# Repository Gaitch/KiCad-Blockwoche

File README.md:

# KiCad-Blockwoche

## Installation

Unter Debian/Ubuntu kann KiCad mit den folgenden Befehlen installiert werden:

```sh
sudo apt install -t bookworm-backports kicad kicad-symbols kicad-footprints kicad-packages3d
```

---

## Tag 1

### Erste Schritte & Einstellungen

- Beim ersten Start die **globale Bibliotheksauswahl** auf Standard belassen.

### Steuerung

#### **Schaltplan-Editor**

- `A` – Bauteil hinzufügen
- `R` – Bauteil rotieren
- `X` – Bauteil spiegeln
- `W` – Draht/Wire zeichnen
- `E` – Bauteil bearbeiten
- `V` – Wert eines Bauteils ändern
- `G` – Bauteil verschieben (ohne Drähte zu trennen)
- `M` – Bauteil verschieben (mit Drähten)
- `Del` – Bauteil oder Draht löschen
- `Ctrl + Z` – Rückgängig machen

#### **PCB-Designer**

- `X` – Leiterbahnen (Traces) zeichnen
- `M` – Bauteil verschieben
- `R` – Bauteil rotieren
- `Ctrl + M` – Bauteil mit Relativbewegung verschieben
- `Ctrl + Z` – Rückgängig machen
- `Ctrl + Y` – Wiederholen
- `Del` – Element löschen

### Workflow

1. **Schaltplan zeichnen**
2. **Elektrische Regelprüfung (ERC) durchführen**
3. **Bauteile im Layout-Editor platzieren**
4. **Leiterbahnen routen** (komponenten verbinden)

### Wichtige Learnings

- Nach der **Zuweisung von Footprints**:
    - **Bauteile kopieren & Werte ändern, ohne die Teilenummern anzupassen, führt zu Problemen** bei der Fertigung.
- **Alle Power-Labels benötigen eine Power-Flag** (`pwr_flag`), damit die elektrische Regelprüfung keine Fehler meldet.

---

## Tag 2

### Arbeiten mit Symbolen

- Symbole können über den **Symbol-Importer** importiert werden.
- Nach dem Import sollte die Zuweisung von Symbolen zu den jeweiligen Footprints überprüft werden.

mit dem druekcen von e mit unselektiertem curses lassen sich die values aendern. und informationen wie 
datenblaetter und bestell informationen hinterlegen

### Shortcuts
p place pin  
e edit properties  

### Zusätzliche Tipps

- **Bibliotheksverwaltung:**
  - Falls benötigte Symbole oder Footprints fehlen, können eigene Bibliotheken angelegt werden.
  - Externe **KiCad-Bibliotheken** können über `Preferences → Manage Symbol Libraries` hinzugefügt werden.

### Datenbank

#### Treiber herunterladen und Installieren

```sh
sudo apt-get install iodbc
```

[https://www.unixodbc.org/](https://www.unixodbc.org/)

```sh
./configure
make
make install
```

[http://www.ch-werner.de/sqliteodbc/](http://www.ch-werner.de/sqliteodbc/)  
[http://www.ch-werner.de/sqliteodbc/html/index.html](http://www.ch-werner.de/sqliteodbc/html/index.html)

```sh
./configure && make
make install
```

#### Treiber Registrieren

```sh
sudo odbcinst -i -s -f /etc/odbc.ini
sudo odbcinst -i -d -f /etc/odbcinst.ini
```

Datenbank in KiCad hinzufügen. Wenn die Treiber korrekt installiert wurden, sollte keine Fehlermeldung auftauchen und die Komponenten tauchen mit dem gegebenen Namen in der Part-Selektion auf.

Neue Komponenten müssen dann über ein Datenbank-Tool in die Datenbank geschrieben werden. Die Symbole werden in KiCad erstellt und dann in der Datenbank verknüpft.

**Tabellenstruktur Datenbank**

| Feldname         | Beschreibung                                                    |
|-----------------|----------------------------------------------------------------|
| PartID          | Eindeutige ID des Bauteils in der Datenbank                    |
| Symbol         | Referenz auf das Schaltplansymbol                               |
| Footprint       | Zugehöriges Footprint-Modell für die Platine                   |
| Value           | Bauteilwert (z. B. Widerstandswert, Kapazität)                 |
| Designator      | Bezeichnung des Bauteils im Schaltplan (z. B. R1, C3, U5)      |
| Category        | Bauteilkategorie (z. B. Widerstand, Kondensator, IC)           |
| MFR             | Hersteller (Manufacturer) des Bauteils                         |
| MPN             | Herstellernummer (Manufacturer Part Number)                    |
| Rating          | Elektrische Spezifikationen des Bauteils (z. B. Spannung, Strom) |
| Remark         | Zusätzliche Anmerkungen oder Hinweise                          |
| Datasheet       | Link oder Pfad zum Datenblatt des Bauteils                     |
| Dist1           | Distributor 1 (Händler für das Bauteil)                        |
| Dist1PN         | Teilenummer bei Distributor 1                                  |
| Dist2           | Distributor 2                                                 |
| Dist2PN         | Teilenummer bei Distributor 2                                 |
| Dist3           | Distributor 3                                                 |
| Dist3PN         | Teilenummer bei Distributor 3                                 |
| Active          | Gibt an, ob das Bauteil aktiv oder abgekündigt ist             |
| Description     | Detaillierte Beschreibung des Bauteils                         |
| FootprintFilters | Filter für alternative Footprints                             |
| Keywords        | Stichworte für die Suche nach dem Bauteil                      |
| NoBom           | Gibt an, ob das Bauteil in die Stückliste (BOM) aufgenommen wird |
| SchematicOnly   | Bauteil existiert nur im Schaltplan, nicht auf der Platine     |
| Version         | Versionsnummer des Bauteils in der Datenbank                   |
| Created        | Datum der Erstellung des Bauteileintrags                        |
| Modified       | Datum der letzten Änderung des Bauteileintrags                  |

---

## Tag 3

### Arbeiten mit großen Schaltplänen

#### Schaltpläne über mehrere Seiten aufteilen
- Ermöglicht eine bessere **Strukturierung** und **Übersichtlichkeit**.
- Besonders hilfreich für **komplexe Schaltungen** mit vielen Komponenten.

#### Verwendung von Labels für Verbindungen
- Durch die Nutzung **gleichnamiger Labels** können Signale und Netze zwischen verschiedenen Seiten eines Schaltplans verbunden werden.
- Dies **ersetzt lange Drahtverbindungen** und sorgt für eine **saubere Darstellung**.  
  **Globale und lokale Labels beachten.**

#### Hierarchische Schaltpläne verwenden
- **Module** können in **separaten Hierarchieblöcken** organisiert werden.
- Erleichtert das **Wiederverwenden** von Schaltungsblöcken.
- **Verbessert die Lesbarkeit** des Schaltplans.

#### Netzklassen definieren
- **Netzklassen** helfen, verschiedene Signalarten (z. B. **Stromversorgung, Signalleitungen, Hochfrequenzleitungen**) zu organisieren.
- Dies erleichtert das **Einhalten von Design-Richtlinien** und **DRC-Prüfungen**. Diese können dann beim Layout eingestellt werden.

**(Zuweisungen ergänzen)**

#### BUS erstellen
- **Dicke blaue Leitung** zeichnen.
- **Label hinzufügen** und Bus-Elemente angeben (Example: `B0 - 13, CLK, IO`). Label name B[0..15]
- **Rechtsklick auf Bus → Unfold** wählen und dann die einzelnen Pins verbinden.
- **Bus-Aliase** können in den **Blatteigenschaften** neben dem Speichersymbol hinzugefügt werden.

#### Electrical Rule Check (ERC) Einstellungen
- **Input zu Input gibt keinen Fehler**. Diese sind einstellbar.

#### Capacity Bias Effect
- **Kapazitive Effekte durch Layout beachten.**
erklaeren was es macht.. hoehere spannung kleine kapazitaet

#### Pin Helper
- **Rechtsklick auf einen Pin → Pin Helper** wählen.
- **Label und Pin** direkt zuweisen.

### Footprints

- **3D-Modelle hinzufügen**, um Footprints visuell zu überprüfen.
- **Abmessungen aus Datenblättern entnehmen**.
- **Pads erstellen** mit dem Kreis-Icon.
- **Doppelklick auf ein Pad**, um **Größe und Position** festzulegen.
- **Eingabefelder unterstützen Berechnungen** (z. B. `5mm + 2mm`).

#### Zusätzliche Ebenen
- **Fab-Layer** für Fertigungsinformationen.
- **Silkscreen-Layer** für Beschriftungen auf der Platine.
- **Margin-Layer** zur Definition von Platinenrändern.

## Tag 4

### Vias
Bei Vias müssen einige Dinge beachtet werden, unter anderem:
- **Lagenaufbau und Möglichkeiten** → Vorab den **Produzenten** wählen und abklären.
- **Auswirkungen** → Kosten & Produktionszeit berücksichtigen.
- **Minimale Lochdurchmesser** → Typisch **0.3 mm**.
- **Restring** → Typisch **0.15 mm**.
- **Keine Vias im Pad** → Lötzinn fließt weg, außer verschlossen (→ teuer!).

---

### Einstellungen
**Pfad:** *File → Board-Setup*

#### **Physical Stackup**
- Anzahl **Layer** und deren **Eigenschaften/Konfiguration** festlegen.

#### **Constraints**
- Design-Regeln und **Mindestabstände** definieren.

#### **Netzklassen**
- **Gruppierung von Signalen** (z. B. **Power, GND, Signal**).

#### **Custom Rules**
- **Eigene Design-Regeln** für spezifische Anforderungen erstellen.

---

### PCB Designer

#### **Bauteile importieren**
- Fehlermeldungen beachten → zeigen **fehlende Footprints** oder andere **Komplikationen**.

#### **Schritt 1: Board zeichnen**
- **Edge Cuts** Layer für die **Platinenkontur** nutzen.

#### **Schritt 2: Bauteile platzieren**
- **Grob platzieren**, dann **Feinjustierung**.
- **Zentrale Komponenten zentrieren** (z. B. Mikrocontroller).
- **Ausrichtung beachten** → USB-Pins zum **USB-Stecker**.
- **Abstände einhalten**:
  - **Digitale und analoge Bereiche trennen**.
  - **Kurze Verbindungen für empfindliche Signale**.
  - **Kondensatoren möglichst nah an ICs platzieren**.

---

### **Tipps**
- **Nur Footprints selektierbar machen**, um **versehentliches Verschieben** von Verbindungen zu vermeiden.

Einige Bauteile wie Spannungsregulatoren oder Oszillatoren geben gewisse Anordnungen der Bauteile vor. Diese gemaess Datenblatt anordnen und verbinden.

---

### **Frage**
> Ist es möglich, nachträglich einen **Footprint** hinzuzufügen, sodass er automatisch mit bereits im **Schaltplan vorhandenen Bauteilen** synchronisiert wird?

## Tag 5

### **Flächen & Polygone (Filled Zones)**
- **Bereich zeichnen**, um eine gefüllte Kupferfläche zu erstellen.
- **Verbindung wählen** → Typischerweise **Speisung (VCC) oder Ground (GND)**.
- **Mit `B` neu generieren**, um die Zone zu aktualisieren.

#### **Eigenschaften der Zone anpassen**
1. **Zone anklicken** und **Eigenschaften öffnen**.
2. Unter **Pad Connection** den **Thermal Relief** Modus wählen.

---

### **Differentielles Layout für USB**
#### **Schritt 1: Netzlabels im Schematic Setup verwalten**
- **USB-Signale** in der **Netclass-Verwaltung** zuweisen.

#### **Schritt 2: Differenzpaar im Layout erstellen**
1. **`6` auf das Pad klicken**.
2. Zwei **parallele Leitungen** sollten automatisch erstellt werden.

---

## **Bill of Material (BOM)**
Die **Stückliste (Bill of Material, BOM)** enthält alle benötigten Bauteile für die Fertigung der Platine. Sie stellt sicher, dass alle Bauteile korrekt bestellt und bestückt werden.

### **Typische Informationen in der BOM**
- **Bauteilbezeichnung** (Designator, z. B. R1, C3, U5)
- **Bauteilwert** (z. B. 10kΩ, 100nF)
- **Footprint** (z. B. SMD0603, THT)
- **Hersteller & Bestellnummer** (MFR, MPN)
- **Distributor & Bestellnummer** (z. B. Mouser, Digikey, LCSC)
- **Anzahl der Bauteile** für die Fertigung

### **Export der BOM in KiCad**
Die BOM kann über **File → Fabrication Outputs → BOM** exportiert werden.  
Es gibt verschiedene **BOM-Plugins**, die z. B. eine CSV oder Excel-Datei generieren.

---

## **Gerber-Dateien**
**Gerber-Dateien** sind das standardisierte Format für die Herstellung von Leiterplatten. Sie enthalten die **grafische Darstellung** der verschiedenen PCB-Layer, die von Herstellern genutzt werden.

### **Typische Gerber-Dateien**
- **Leiterbahnen & Kupferflächen** (z. B. `Top_Copper`, `Bottom_Copper`)
- **Lötstopplack & Bestückungsdruck** (Solder Mask & Silkscreen)
- **Platinenumrisse** (Edge Cuts)

### **Gerber-Export in KiCad**
1. **File → Fabrication Outputs → Gerber**
2. **Alle relevanten Layer auswählen** (Top, Bottom, Silkscreen, Soldermask, etc.).
3. **Gerber-Dateien exportieren und in einem Viewer kontrollieren**.

---

## **Bohrdaten (Drill Files)**
Die **Bohrdaten** definieren alle Löcher, die auf der Platine gebohrt werden müssen. Sie sind besonders wichtig für bedrahtete Bauteile, Vias und Montagelöcher.

### **Typische Inhalte der Bohrdaten**
- **THT-Bohrungen** für bedrahtete Bauteile.
- **Vias** für Lagenverbindungen zwischen PCB-Schichten.
- **Montagelöcher** für Gehäuse oder Befestigungen.

### **Bohrdaten-Export in KiCad**
1. **File → Fabrication Outputs → Drill Files**
2. **Bohrdurchmesser & -typen überprüfen**.
3. **Bohrdateien zusammen mit den Gerber-Dateien an den Hersteller senden**.

---

## **Pick & Place Daten**
Die **Pick & Place Datei** enthält die **Positionen der Bauteile** für die automatische Bestückung mit Maschinen. SMT-Bauteile werden anhand dieser Datei automatisch auf die Platine gesetzt.

### **Typische Inhalte der Pick & Place Datei**
- **X- & Y-Koordinaten** der Bauteile.
- **Drehwinkel der Bauteile**.
- **Footprint & Referenzdesignator** (z. B. `R1`, `C3`).

### **Pick & Place-Export in KiCad**
1. **File → Fabrication Outputs → Footprint Position File**
2. **Format auswählen (CSV, TXT, etc.)**.
3. **Datei an den Bestücker senden**.

---

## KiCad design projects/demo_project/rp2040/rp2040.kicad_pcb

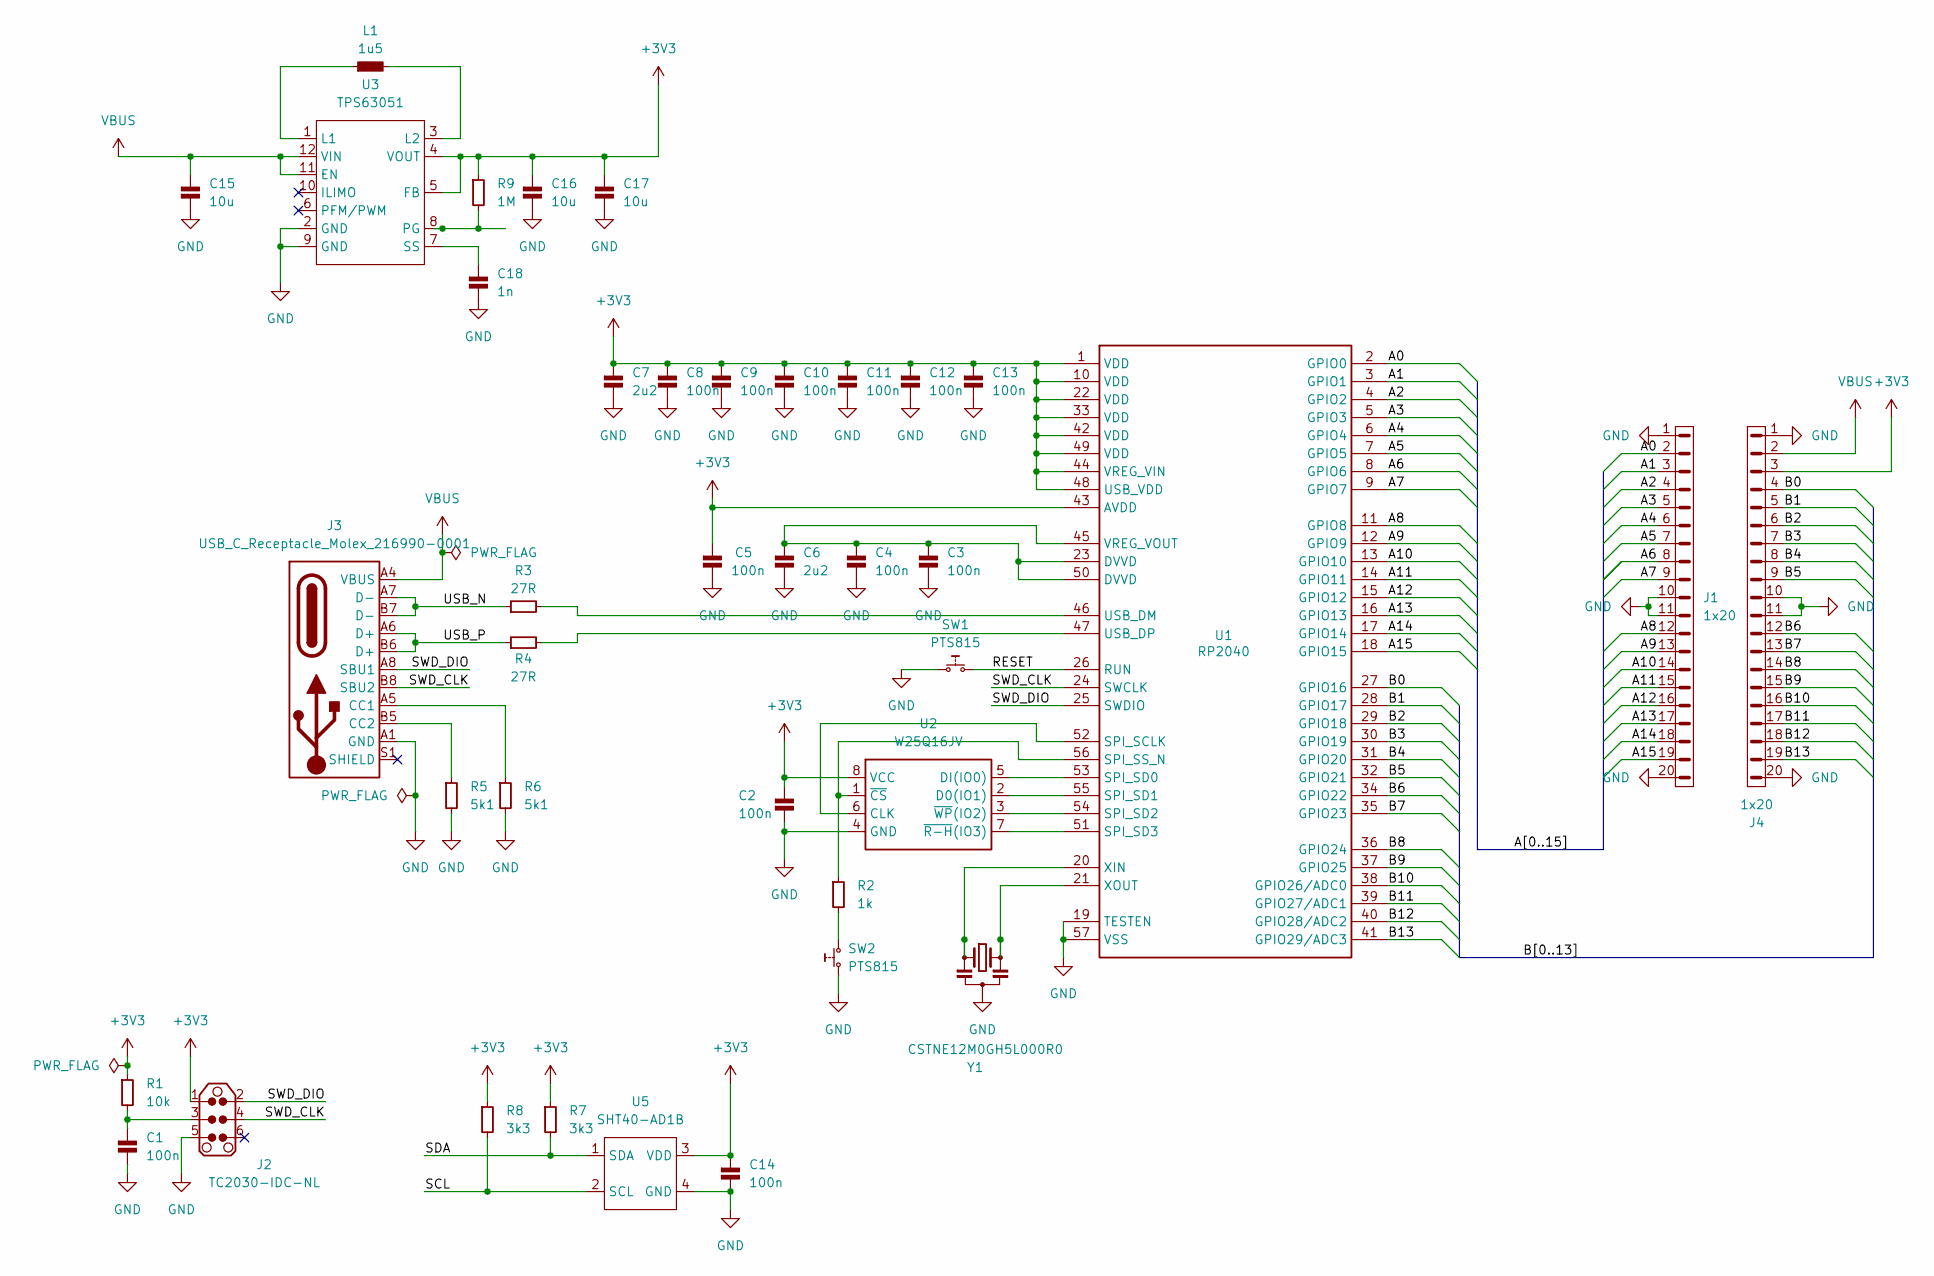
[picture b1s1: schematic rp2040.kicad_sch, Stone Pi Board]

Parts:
C1, C2, C3, C4, C5, C8, C9, C10, C11, C12, C13, C14: 100n; C_0402; Rating 16V, 10%, X7R; MFR# CL21B105KO5NNWC
C6, C7: 2u2; C_0402; Rating 10V, 20%, X5R; MFR# CC0402MRX5R6BB225
C15, C16, C17: 10u; C_0805; Rating 16V, 10%, X5R; MFR# CL21A106KOQNNNF
C18: 1n; C_0402; Rating 16V, 10%, X7R; MFR# CL05B102KO5NNWC
J1, J4: 1x20; PinHeader_1x20_P2.54mm_Vertical; Rating 3A; MFR# 61302011121
J2: TC2030-IDC-NL; MFR# TC2030-IDC-NL
J3: USB_C_Receptacle_Molex_216990-0001; USB_C_Receptacle_MidMnt_Molex_16_Contact_216990-0001; Rating 16 contacts, 1.25A; MFR# 216990-0001
L1: 1u5; L_3.2x2.5; Rating 4A, 20%, 61mOhm; MFR# SRP3212A-1R2M
R1: 10k; R_0402; Rating 50V, 62.5mW, 1%; MFR# RC0402FR-0710KL
R2: 1k; R_0402; Rating 50V, 62.5mW, 1%; MFR# RC0402FR-071KL
R3, R4: 27R; R_0402; Rating 50V, 62.5mW, 1%; MFR# RC0402FR-0727RL
R5, R6: 5k1; R_0402; Rating 50V, 62.5mW, 1%; MFR# RC0402FR-075K1L
R7, R8: 3k3; R_0402; Rating 50V, 62.5mW, 1%; MFR# RC0402FR-073K3L
R9: 1M; R_0402; Rating 50V, 62.5mW, 1%; MFR# RC0402FR-071ML
SW1, SW2: PTS815; TS02-66-Series; Rating -40˚C to 90˚C; MFR# PTS815SJM250SMTR
U1: RP2040; QFN-56-1EP_7x7mm_P0.4mm_EP3.2x3.2mm
U2: W25Q16JV; USON_2x3x0.6mm
U3: TPS63051; VQFN-12-1EP_2.5x2.5mm_P0.5mm; Rating –0.3 to 7; MFR# TPS63051YFFR
U5: SHT40-AD1B; Sensirion_DFN-4_1.5x1.5mm_P0.8mm_SHT4x_NoCentralPad; MFR# SHT40-AD1B-R2
Y1: CSTNE12M0GH5L000R0; Resonator_SMD_Murata_CSTxExxV-3Pin_3.0x1.1mm; Rating 12MHz, 0.07%; MFR# CSTNE12M0GH5L000R0

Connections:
+3V3: C2.1, C5.1, C7.1, C8.1, C9.1, C10.1, C11.1, C12.1, C13.1, C14.1, C16.1, C17.1, J2.1, J4.3, R1.1, R7.1, R8.1, R9.1, U1.1 (VDD), U1.10 (VDD), U1.22 (VDD), U1.33 (VDD), U1.42 (VDD), U1.43 (AVDD), U1.44 (VREG_VIN), U1.48 (USB_VDD), U1.49 (VDD), U2.8 (VCC), U3.4 (VOUT), U3.5 (FB), U5.3 (VDD)
/A0: J1.2, U1.2 (GPIO0)
/A1: J1.3, U1.3 (GPIO1)
/A2: J1.4, U1.4 (GPIO2)
/A3: J1.5, U1.5 (GPIO3)
/A4: J1.6, U1.6 (GPIO4)
/A5: J1.7, U1.7 (GPIO5)
/A6: J1.8, U1.8 (GPIO6)
/A7: J1.9, U1.9 (GPIO7)
/A8: J1.12, U1.11 (GPIO8)
/A9: J1.13, U1.12 (GPIO9)
/A10: J1.14, U1.13 (GPIO10)
/A11: J1.15, U1.14 (GPIO11)
/A12: J1.16, U1.15 (GPIO12)
/A13: J1.17, U1.16 (GPIO13)
/A14: J1.18, U1.17 (GPIO14)
/A15: J1.19, U1.18 (GPIO15)
/B0: J4.4, U1.27 (GPIO16)
/B1: J4.5, U1.28 (GPIO17)
/B2: J4.6, U1.29 (GPIO18)
/B3: J4.7, U1.30 (GPIO19)
/B4: J4.8, U1.31 (GPIO20)
/B5: J4.9, U1.32 (GPIO21)
/B6: J4.12, U1.34 (GPIO22)
/B7: J4.13, U1.35 (GPIO23)
/B8: J4.14, U1.36 (GPIO24)
/B9: J4.15, U1.37 (GPIO25)
/B10: J4.16, U1.38 (GPIO26/ADC0)
/B11: J4.17, U1.39 (GPIO27/ADC1)
/B12: J4.18, U1.40 (GPIO28/ADC2)
/B13: J4.19, U1.41 (GPIO29/ADC3)
/RESET: SW1.2, U1.26 (RUN)
/SCL: R8.2, U5.2 (SCL)
/SDA: R7.2, U5.1 (SDA)
/SWD_CLK: J2.4, J3.B8 (SBU2), U1.24 (SWCLK)
/SWD_DIO: J2.2, J3.A8 (SBU1), U1.25 (SWDIO)
/USB_N: J3.A7 (D-), J3.B7 (D-), R3.1
/USB_P: J3.A6 (D+), J3.B6 (D+), R4.1
GND: C1.2, C2.2, C3.2, C4.2, C5.2, C6.2, C7.2, C8.2, C9.2, C10.2, C11.2, C12.2, C13.2, C14.2, C15.2, C16.2, C17.2, C18.2, J1.1, J1.10, J1.11, J1.20, J2.5, J3.A1 (GND), J3.A12 (GND), J3.B1 (GND), J3.B12 (GND), J4.1, J4.10, J4.11, J4.20, R5.2, R6.2, SW1.1, SW2.1, U1.19 (TESTEN), U1.57 (VSS), U2.4 (GND), U3.2 (GND), U3.9 (GND), U5.4 (GND), Y1.2
unnamed: C1.1, J2.3, R1.2
unnamed: J3.A5 (CC1), R6.1
unnamed: J3.B5 (CC2), R5.1
unnamed: R2.2, SW2.2
unnamed: U1.52 (SPI_SCLK), U2.6 (CLK)
unnamed: U1.53 (SPI_SD0), U2.5 (DI(IO0))
unnamed: U1.55 (SPI_SD1), U2.2 (D0(IO1))
unnamed: U1.54 (SPI_SD2), U2.3 (~WP(IO2))
unnamed: U1.51 (SPI_SD3), U2.7 (~R-H(IO3))
unnamed: R2.1, U1.56 (SPI_SS_N), U2.1 (~CS)
unnamed: R3.2, U1.46 (USB_DM)
unnamed: R4.2, U1.47 (USB_DP)
unnamed: C3.1, C4.1, C6.1, U1.23 (DVVD), U1.45 (VREG_VOUT), U1.50 (DVVD)
unnamed: U1.20 (XIN), Y1.1
unnamed: U1.21 (XOUT), Y1.3
unnamed: L1.1, U3.1 (L1)
unnamed: L1.2, U3.3 (L2)
unnamed: R9.2, U3.8 (PG)
unnamed: C18.1, U3.7 (SS)
VBUS: C15.1, J3.A4 (VBUS), J3.A9 (VBUS), J3.B4 (VBUS), J3.B9 (VBUS), J4.2, U3.11 (EN), U3.12 (VIN)

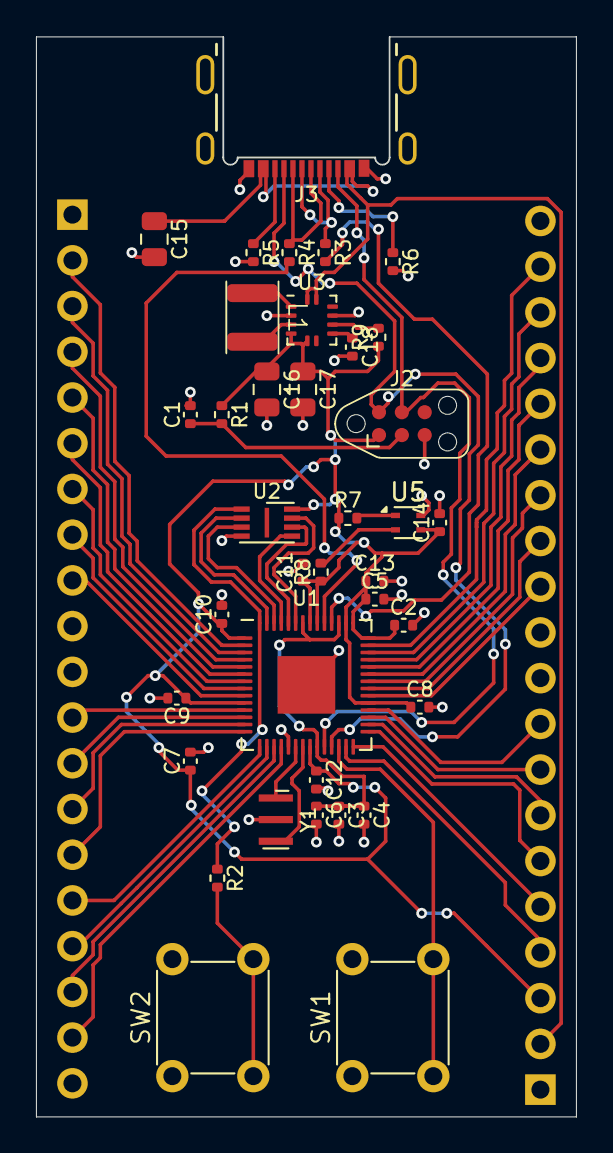
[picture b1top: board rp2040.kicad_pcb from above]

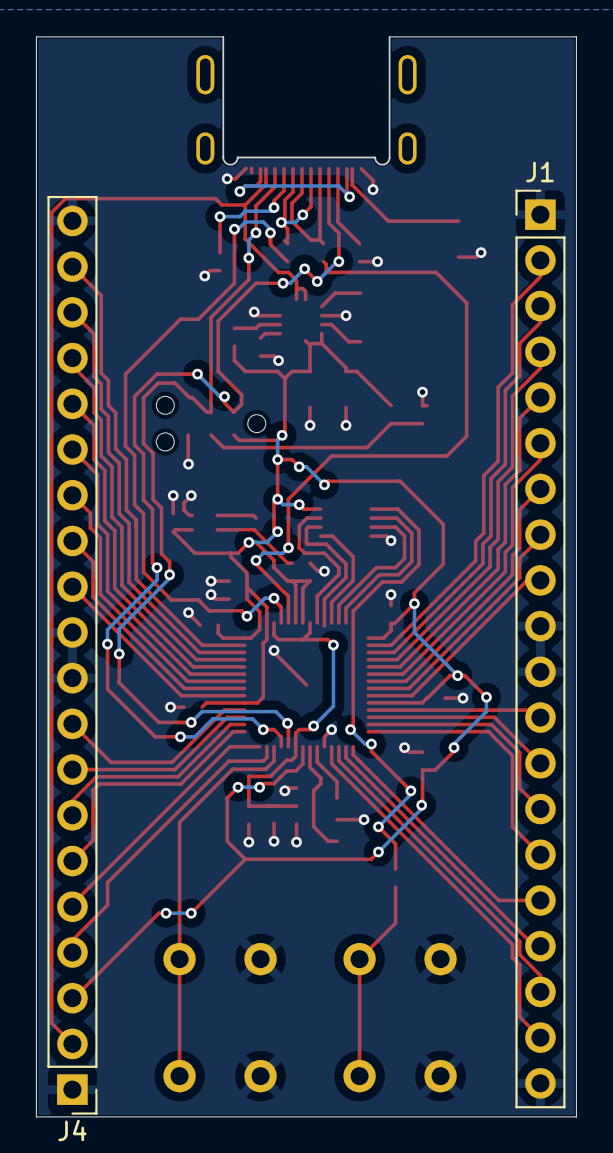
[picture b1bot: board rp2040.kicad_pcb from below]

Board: 2 copper layers, 30.0 x 60.0 mm, 39 parts (2 on the bottom side), 59 nets.

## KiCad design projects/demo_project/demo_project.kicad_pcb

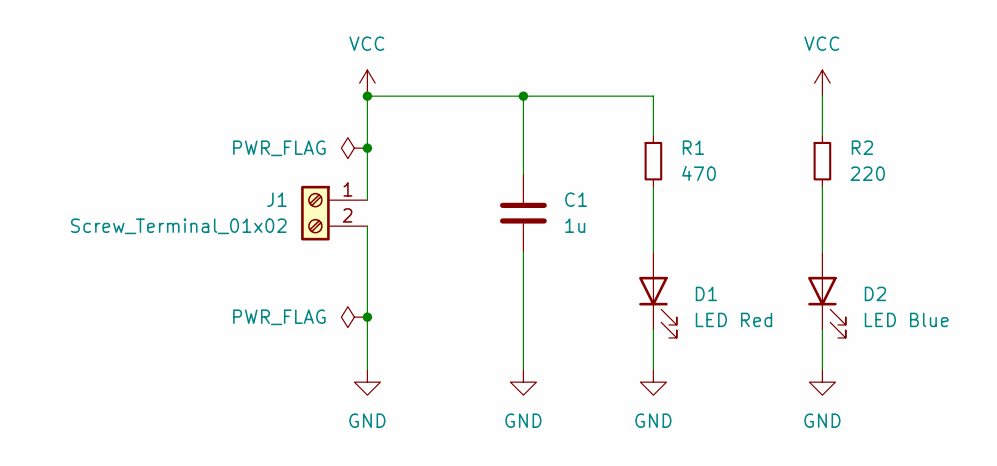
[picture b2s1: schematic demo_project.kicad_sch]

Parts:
C1: 1u; C_0805_2012Metric_Pad1.18x1.45mm_HandSolder
D1: LED Red; LED_0805_2012Metric_Pad1.15x1.40mm_HandSolder
D2: LED Blue; LED_0805_2012Metric_Pad1.15x1.40mm_HandSolder
J1: Screw_Terminal_01x02; TerminalBlock_Altech_AK300-2_P5.00mm
R1: 470; R_0805_2012Metric_Pad1.20x1.40mm_HandSolder
R2: 220; R_Axial_DIN0922_L20.0mm_D9.0mm_P25.40mm_Horizontal

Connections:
GND: C1.2, D1.1 (K), D2.1 (K), J1.2
unnamed: D1.2 (A), R1.2
unnamed: D2.2 (A), R2.2
VCC: C1.1, J1.1, R1.1, R2.1

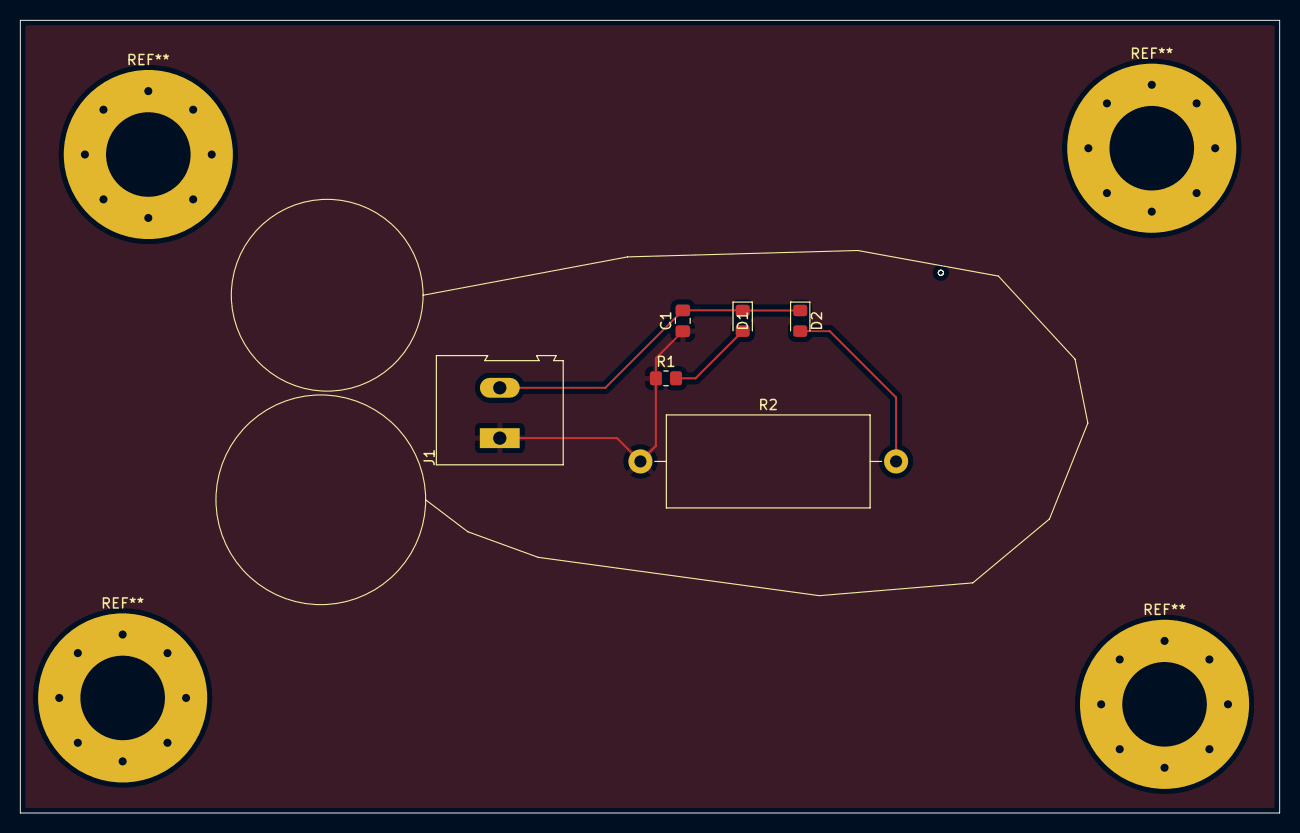
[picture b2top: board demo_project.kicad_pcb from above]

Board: 2 copper layers, 125.1 x 78.7 mm, 6 parts (0 on the bottom side), 4 nets.

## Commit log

2025-02-10 create demo schematic
2025-02-10 assign footprints
2025-02-10 add content to readme for day one
2025-02-10 create layout of the pcb design
2025-02-10 day one summary
2025-02-11 add database documentation
2025-02-11 add database
2025-02-12 schematic for new project stone board
2025-02-12 footprints
2025-02-12 add day 3
2025-02-12 update library
2025-02-13 finish schematic and route gpio traces
2025-02-13 rout secondary components
2025-02-13 add documentation for day four
2025-02-14 finish layout
2025-02-14 finish doc
2025-02-19 generate export files and change trace thicknes for tps v-reg
